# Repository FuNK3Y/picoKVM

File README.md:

# PicoKVM
An inexpensive network KVM that can switch USB and monitor inputs simultaneously

## Why
Samsung makes great monitors, but they often lack a KVM. The project started as a way to switch them along with the USB devices, over their network API. It was later generalized to most monitors, driven over HDMI DDC/CI by its own board, while still driving network-controlled monitors and devices.

## Features
- Switches the USB devices and the monitors' inputs together
- Drives most monitors over HDMI DDC/CI, and others (or any device: a lamp, ...) over the network
- No video goes through it: every computer is connected directly to every monitor, so HDCP, VRR, G-Sync, FreeSync, HDR, ... work natively
- Controlled from its button, a web page or an HTTP API, from any device on the network

## Hardware
picoKVM runs on its own board, designed in [`hardware/`](hardware/README.md): an ESP32-S3, a USB 3.0 switch (two computers, one peripheral port), two HDMI ports carrying DDC/CI only (no video) to switch monitor inputs, an RGB status LED, and a Grove port for an [M5Stack key unit](https://shop.m5stack.com/products/mechanical-key-button-unit) as the switch button.

The original build (M5Stack AtomS3 Lite + USB multiplexer) is no longer supported; its last version is [5d5997c](https://github.com/FuNK3Y/picoKVM/tree/5d5997c).

## Install
1. Open the **[browser installer](https://funk3y.github.io/picoKVM/)** in Chrome or Edge, and plug the board's AUX / FLASH USB-C port into the computer.
2. Install, then connect the board to your Wi-Fi from the same page.
3. *Visit device* opens the [settings page](#settings): set the [admin password](#admin-password) first, then the input names and the monitors.

## Wiring
- Computers' video goes directly to the monitors, as without a KVM.
- Each computer's USB goes to the board; the keyboard and mouse go to its peripheral port, through a hub (the monitor's own hub works).
- For monitors driven over DDC/CI, an HDMI cable goes from one of the board's HDMI ports to the monitor. It carries only the input-switch commands, no video. Monitors driven over the network need none.

```mermaid
graph LR
    KB["Keyboard"] <--> |USB| HUB["USB hub"]
    MOUSE["Mouse"] <--> |USB| HUB
    KVM <--> |USB| HUB
    PC1["Computer 1"] --> |Video| MON["Monitor"]
    PC2["Computer 2"] --> |Video| MON
    PC1 <--> |USB| KVM["picoKVM"]
    PC2 <--> |USB| KVM
    KVM -.-> |"HDMI (DDC/CI only)"| MON
    style MON fill:#f9f,stroke:#333
    style KVM fill:#bbf,stroke:#333
    style HUB fill:#ddd,stroke:#333
    style KB fill:#ddd,stroke:#333
    style MOUSE fill:#ddd,stroke:#333
    style PC1 fill:#ddd,stroke:#333
    style PC2 fill:#ddd,stroke:#333
```

## Settings
The settings page (*Settings*, below the switch button at `http://picokvm.local`) edits everything: Wi-Fi, input names and colors, LED brightness, admin password, monitors and [updates](#updates).

### Admin password
Once set, the admin password protects everything the settings page does: opening it, reading and changing the configuration, and installing updates, from the page or through the API. The browser asks for it (any user name); API calls send it as HTTP Basic credentials, e.g. `curl -u admin:<password>`. Switching inputs, the state and `/metrics` stay open.

**Until it is set, all of that is open to anyone on the network.**

To remove it, use *Clear password*, then *Save*, on the settings page, or send `"admin_password": null` to `/api/config`; everything above is then open again.

It travels over plain HTTP, so anyone able to watch the network traffic can read it.

### Monitors
Monitors are added on the settings page: a form for DDC/CI monitors, JSON for the others ([`config.example.json`](config.example.json) has an example of each).

#### DDC/CI monitors
Enable DDC/CI in the monitor's menu. For each computer, choose the monitor input it is on. The settings page reads the monitor: its name, the input it is on now, and the inputs it lists, named as the MCCS standard names them (VCP `0x60`: `15` DisplayPort 1, `17` HDMI 1, ...). Some monitors use other values, or name their ports differently: put the monitor on each computer's input by hand, and the page shows which value it is (*Other value...* takes any number). *Power the monitor on first* wakes up monitors that keep DDC/CI alive in standby.

The monitor must accept DDC/CI on an input that is not the active one, since it is showing the other computer when the command arrives. Most do: tested on **AOC, Samsung, Dell, Acer, Philips and Lenovo** monitors. Some have no DDC/CI at all (the Samsung G80SD): drive those over the network.

#### Samsung monitors over the network
For Samsung smart monitors without DDC/CI, the KVM sends remote-control key presses: enable IP remote on the monitor *(Connection > Network > Expert Settings)*. Find a repeatable sequence of keys that selects each input from the home screen, and write it with the [key codes](https://github.com/ollo69/ha-samsungtv-smart/blob/master/docs/Key_codes.md) as a `SamsungMonitor`. `KEY_RETURN` first also wakes the monitor up; `command_delay` (or a `delay` on one key) slows the sequence down if the menu cannot keep up.

#### Other network devices
A `GenericDevice` sends an HTTP request for each input: another monitor's API (e.g. [SmartThings](https://github.com/ollo69/ha-samsungtv-smart/issues/274#issuecomment-2597627685), untested), a lamp, ...

## Use
Switch with the button, the web page at `http://picokvm.local` (it follows the KVM whoever switches it), or the API:
```sh
curl -X POST http://picokvm.local/api/active_input/A   # or B; without the input, toggles
curl http://picokvm.local/api/active_input             # the state: active input, switching, last error
curl http://picokvm.local/api/events                   # the state as server-sent events, on every change
```
`/api/config` reads (`GET`) and writes (`POST`) the configuration, without the passwords, only `admin_password_set` tells whether one is set ([admin password](#admin-password) required). `/metrics` gives Wi-Fi signal, memory, USB power and version for Prometheus.

`picokvm` is the default hostname; it can be changed in the settings.

## Updates
*Check for updates*, then *Install*, on the settings page installs the latest [release](https://github.com/FuNK3Y/picoKVM/releases) over the network; *Upload* installs a `firmware-ota.bin` of your own. Settings are kept. The first boot of an update is a trial: if the device is not back on Wi-Fi within 2 minutes, it returns to the previous firmware.

The same through the API, with the [admin password](#admin-password):
```sh
curl -u admin:<admin_password> -X POST http://picokvm.local/api/update/latest
curl -u admin:<admin_password> --data-binary @firmware-ota.bin http://picokvm.local/api/update
```

MicroPython does not check GitHub's certificate when downloading a release: the SHA-256 GitHub publishes only guards against a corrupted download.

## ESPHome
The board can also run [ESPHome](https://esphome.io) instead of this firmware, for a native Home Assistant integration (DDC/CI monitors only). Include the [esphome/picokvm.yaml](esphome/picokvm.yaml) package, then name the computers and set the number of monitors:

```yaml
packages:
  picokvm: github://FuNK3Y/picoKVM/esphome/picokvm.yaml@main

substitutions:
  inputs:
    a: Work laptop
    b: Gaming PC
  monitors: 2
```

Each monitor's input values and the LED colors and brightness are then set from Home Assistant. [esphome/example.yaml](esphome/example.yaml) is a complete starting point; it builds, but has not been run on a board yet.

## Development
[`firmware/build.sh`](firmware/build.sh) builds MicroPython with `src/` frozen in, into `firmware/build/` (needs [ESP-IDF](https://docs.espressif.com/projects/esp-idf/en/v5.5.2/esp32s3/get-started/) v5.5.2):
```sh
. $IDF_PATH/export.sh
firmware/build.sh
```
CI runs the same build on pull requests and `main` and keeps the images as an artifact. A `v*` tag publishes a release and the [installer](install/index.html) to GitHub Pages.

The tests run the application on CPython, with stand-ins for the board ([`tests/mocks.py`](tests/mocks.py)); CI requires 95% coverage:
```sh
python3 -m unittest discover -s tests
```

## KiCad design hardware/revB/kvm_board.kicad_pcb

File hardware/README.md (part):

# picoKVM board — ESP32-S3 USB 3.0 KVM switch with HDMI DDC/CI

Two PCs (USB 3.0 Type-B) share one peripheral port (USB 3.0 Type-A).  An
ESP32-S3 flips the USB path and tells both monitors to change input over
HDMI DDC/CI.  The HDMI ports carry DDC/+5V only — video goes straight
from the PCs to the monitors.  The firmware is the MicroPython code in
`src/`, built into a MicroPython image by `firmware/` (see the main [README](../README.md)).

## Rev A release (ordered 2026-10-03, JLCPCB)

`revA/` holds the board exactly as it was sent to JLCPCB.  Freerouting is not
deterministic, so **`revA/kvm_board.kicad_pcb` is the design of record**: a
fresh `./build.sh` produces an equivalent board, not the same copper.

| file | what |
|---|---|
| `revA/kvm_board.kicad_pcb` / `.kicad_pro` / `.kicad_dru` | routed board (KiCad 10), its net classes and JLC design rules |
| `revA/jlcpcb/gerbers.zip`, `bom.csv`, `cpl.csv` | the files uploaded to JLCPCB (126 × 75 mm customer panel) |
| `revA/schematic_review.html` | readable schematic: every pin, its net and what else is on it |
| `revA/mechanical.txt` | connector, LED and button positions for the enclosure |
| `revA/thermal_justification.md` | proof that every single-spoke GND pad reaches the In1 plane |
| `revA/impedance.txt` | field-solver results for the 90 Ω pairs on JLC04161H-3313 |
| `revA/img/` | renders (top, bottom, iso, panel) and the Grove J8 pinout |

JLC order settings: 4 layers, 1.6 mm, **specified stackup JLC04161H-3313**,
no impedance control (accepted risk for prototypes, see below), 0.3 mm vias,
1 oz outer / 0.5 oz inner, flying-probe test, Standard PCBA top side,
**edge rails added by customer**, confirm production file and parts placement.

To regenerate the order files from the released board without re-routing:

```
mkdir -p out && cp revA/kvm_board.kicad_* out/
./build.sh fab        # panel (hw/panel.py), Gerbers, PTH/NPTH drill, BOM, CPL -> out/jlcpcb/
```

## Rev B (order files ready, branch `rev-b`)

`revB/` holds the board as it is to be sent to JLCPCB.  As for rev A,
**`revB/kvm_board.kicad_pcb` is the design of record**: `./build.sh` routed
it to 6 open connections, and the last ones were closed by hand on the routed
board (local rip-up and re-lay of a few control lines around the hub's
north-east pins and the RP2350's QSPI bus, gap joins on the VBUS trunks, port
3's VBUS widened in place, three dangling vias removed).  A fresh build gives
an equivalent placement, not this copper.

| file | what |
|---|---|
| `revB/kvm_board.kicad_pcb` / `.kicad_pro` / `.kicad_dru` | routed board (KiCad 10): DRC 0 errors, 0 unconnected, `checks.py` passed |
| `revB/jlcpcb/gerbers.zip`, `bom.csv`, `cpl.csv` | order files (112 × 102 mm customer panel, rails left and right), JLC DFM checked 2026-11-16 |
| `revB/schematic_review.html` | readable schematic |
| `revB/mechanical.txt` | connector, LED and button positions for the enclosure |
| `revB/impedance.txt` | field-solver results for the 90 Ω pairs |
| `revB/img/` | renders (top, bottom, iso) |

JLC DFM on these files (2026-11-16): the red items are understood and
accepted: pad-to-track 0.073–0.10 mm at 0402 pad corners (JLC reads KiCad's
rounded pads as sharp rectangles; KiCad DRC checks the real shape at 0.1 mm),
0.075 mm via annular rings (JLC minimum 0.05 mm), THT-to-SMD spacing at the
HDMI stacks, thermal vias under the RP2350, edge connectors at the edge, and
lead-edge flags on fine-pitch parts ("pin without pad" and "missing hole" are
0).  Check the J1/U11 and J8/J11 3D-model collision warnings in JLC's viewer
before ordering.  Order settings as rev A (4 layers, JLC04161H-3313, top-side
Standard PCBA, edge rails added by customer).

Port supply path (DC resistance of the routed copper, 1 oz outer, from
`revB/kvm_board.kicad_pcb`): USB A J1 → U4 34 mΩ, U32 → port switches
40–64 mΩ, switches → connectors 8–66 mΩ (port 3 66 mΩ); with all four ports
at 1 A, VBUS_HUB drops 111–152 mV.  Rev B's first routing measured ~0.5 Ω
PC-to-port before the 1 mm trunks (`hw/route_nets.py` POWER_TRUNKS).

Hub decoupling: the TUSB8041's +1V1 pins drop through vias onto a B.Cu ring
under the package; C71 sits in the hub's south-west corner (U43 moved down
its USB 2.0 line to make room), 3–8 mm from the west-side pins 5/8/13/21.  A
north-west corner capacitor was tried and dropped: it left the hub's
east-side control lines unroutable.

Rev B adds a TUSB8041 hub with four downstream ports (two stacked USB 3.0
Type-A, J3 and J10), an RP2350 that can intercept the keyboard on port 4,
**four HDMI DDC/CI ports on two stacked connectors** (J5, J6: Foxconn
QJ11191-DFB2-4H) and a TCA9548A I2C multiplexer for the four DDC buses, the
hub's SMBus and a second Grove port.
Pinout changes are under "Rev B: differences from rev A" below.  Several rev A
sections further down no longer describe this board:

| rev A statement below | rev B |
|---|---|
| Board 112 × 75 mm | **98 × 102 mm**, same 4-layer JLC04161H-3313 stackup, top-side assembly |
| Two single HDMI receptacles | Two stacked HDMI receptacles: J5 lower = HDMI 1, upper = HDMI 3; J6 lower = HDMI 2, upper = HDMI 4 (each port with its own 100 mA PTC, USBLC6 and 2k pull-ups; one LM66100 per connector feeds both its ports) |
| No AC-coupling caps on the SuperSpeed lines | The hub's downstream and upstream TX pairs are AC-coupled on the board (C60–C69); the PC-side mux path is unchanged |
| All SuperSpeed pairs on F.Cu | Ports 1/3 RX pairs run partly on B.Cu (referenced to In2 +3V3) |
| ESP32 footprint is the only exposed pad with vias | U30 (hub) and U45 (RP2350) use KiCad's ThermalVias footprints |
| U5 AP2112K LDO, one peripheral port behind U20 | 3.3 V and 1.1 V from two TLV62569 bucks (U5, U31); one TPS2553 per port (U33–U36) behind U32 |
| Prototype test plan (rev A) | see the rev B envelope below |

How the rev B board is laid out and routed, in addition to "How the board is
routed": capacitors and resistors that belong at a pin are tagged in the
schematic (`at=(ref, pin)` in `hw/kvm_board.py`) and placed there by
`make_pcb.py`; `layout.py` keeps routing corridors free of passives (pairs,
the hub's east-side lines, the RP2350's USB escape); `hw/route_nets.py`
pre-routes the nets Freerouting kept leaving open (regulator switch nodes and
feedback, both crystals, the hub's port-control lines, QSPI, the RP2350's USB)
and ties the +1V1 vias into one tree.  The CPL check in `make_fab.py` compares
JLC's pin names with ours (`hw/lib/jlcref/lcsc_pins.json`) and turns D5
(C2286, whose JLC symbol numbers the anode as pin 1) by 180°.

### Rev B prototype power envelope

The four ports can ask for more current than the board's shared supply path
can give: four TPS2553 limits (1.2–1.38 A each) behind one TPS2116 (2.5 A
class), fed by one PC port (0.9 A for USB 3) or the AUX input, and U32 falls
back from AUX to the selected PC the moment AUX goes away.  There is no
aggregate current limit.  Until that is designed in, rev B prototypes are run
inside this envelope:

- **Downstream load, all four ports together: ≤ 0.5 A** (keyboard, mouse and
  low-current devices), whether or not AUX is plugged in, since unplugging
  AUX moves the whole load onto the selected PC.  Measure the board's own
  current on the first prototype and lower the 0.5 A by whatever it exceeds
  0.35 A.
- **No bus-powered drives, chargers or four-port full-load tests, not even
  from a strong bench supply on AUX:** the load still goes through U32 (2.5 A
  class) and the board's shared copper, and falls back onto the selected PC
  when AUX is unplugged.  A higher-current experiment needs its own test plan
  (current-limited source, no PC attached).  Start with no downstream load
  until the board's own current has been measured in its operating states
  (idle, all HDMI monitors attached, Grove modules, ESP32 Wi-Fi active).
- **Grove I2C (J11):** only modules powered from the board's own J11 5 V.  An
  independently powered module with pull-ups to its own 5 V leaks ~0.2 mA per
  line into +3V3, or ~0.5 mA into an unpowered board.
- **HDMI +5 V (pin 18):** measure it with each monitor; it can fall below the
  4.8 V minimum from a weak PC port, as on rev A.  Four monitors can draw up
  to 4 × 55 mA = 0.22 A from +5V_SYS: count it in the board's own current.
- **Port power-off is not a power cycle:** the TPS2553s have no output
  discharge, so a port's 44 µF can hold VBUS well past 200 ms with a light
  load.  Firmware treats a hub reset / port disable as a data disconnect only.
- **Bring-up checks beyond rev A's:** hub enumeration from cold several times
  (crystal start-up); USB 3 and USB 2 throughput on every port; VBUS at each
  port at 0.5 A; scope +5V_SYS and VBUS_HUB when plugging the PCs and AUX one
  after another (inrush: ~30 µF on +5V_SYS and 210 µF on VBUS_HUB with no
  current limit), on a protected source.

## Build

```
./build.sh          # netlist + ERC, PCB, routing, DRC, renders, JLCPCB files (all in Docker)
./build.sh noroute  # same, stopping at the placed, unrouted board
./build.sh reroute  # route the board in out/ as placed (placement runs may reorder footprints, which changes routing)
./build.sh autoroute  # one more Freerouting pass on the board in out/
./build.sh parts    # re-import the LCSC symbols/footprints/3D models
./build.sh shell    # shell inside the toolchain (KiCad 10 + SKiDL + easyeda2kicad)
```

Sources:

| file | what |
|---|---|
| `hw/kvm_board.py` | the schematic, as SKiDL code — edit this, not the netlist |
| `hw/make_pcb.py` | builds the 4-layer `.kicad_pcb`: placement, planes, net classes, JLC rules |
| `hw/route_ss.py` | hand-designed USB 3.0 SuperSpeed pairs (coupled, matched, no vias) |
| `hw/route_usb2.py` | hand-designed USB 2.0 pairs (coupled, matched, symmetric via pairs) |
| `hw/finish.py` | power neck-downs + plane fanout before routing; GND stitching after |
| `hw/layout.py` | rev B placement: anchors, hand-placed passives, passive-free corridors, board size |
| `hw/placement_freeze.py` | frozen passive spots from an earlier placement, so routing-relevant positions stay put |
| `hw/pairs.py`, `hw/route_pairs.py` | rev B pair router and the hub's SuperSpeed / USB 2.0 pairs |
| `hw/route_nets.py` | grid pre-router for nets Freerouting left open, the 1 mm VBUS trunks and the +1V1 tree |
| `hw/plot.py` | 2-D plan of a board window (`out/img/plan.svg`) for layout work |
| `hw/route.py` | Freerouting round-trip (Specctra DSN/SES) for everything else |
| `hw/impedance.py` | 2-D field solver for the 90 Ω pairs on the JLC 3313 stackup |
| `hw/make_fab.py` | JLCPCB `bom.csv` / `cpl.csv` (CPL expressed in JLC's own footprint frame) |
| `hw/panel.py` | JLC assembly panel: rails, mouse bites, fiducials, tooling holes |
| `hw/thermal_report.py` | proves every single-spoke GND pad reaches the In1 plane |
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
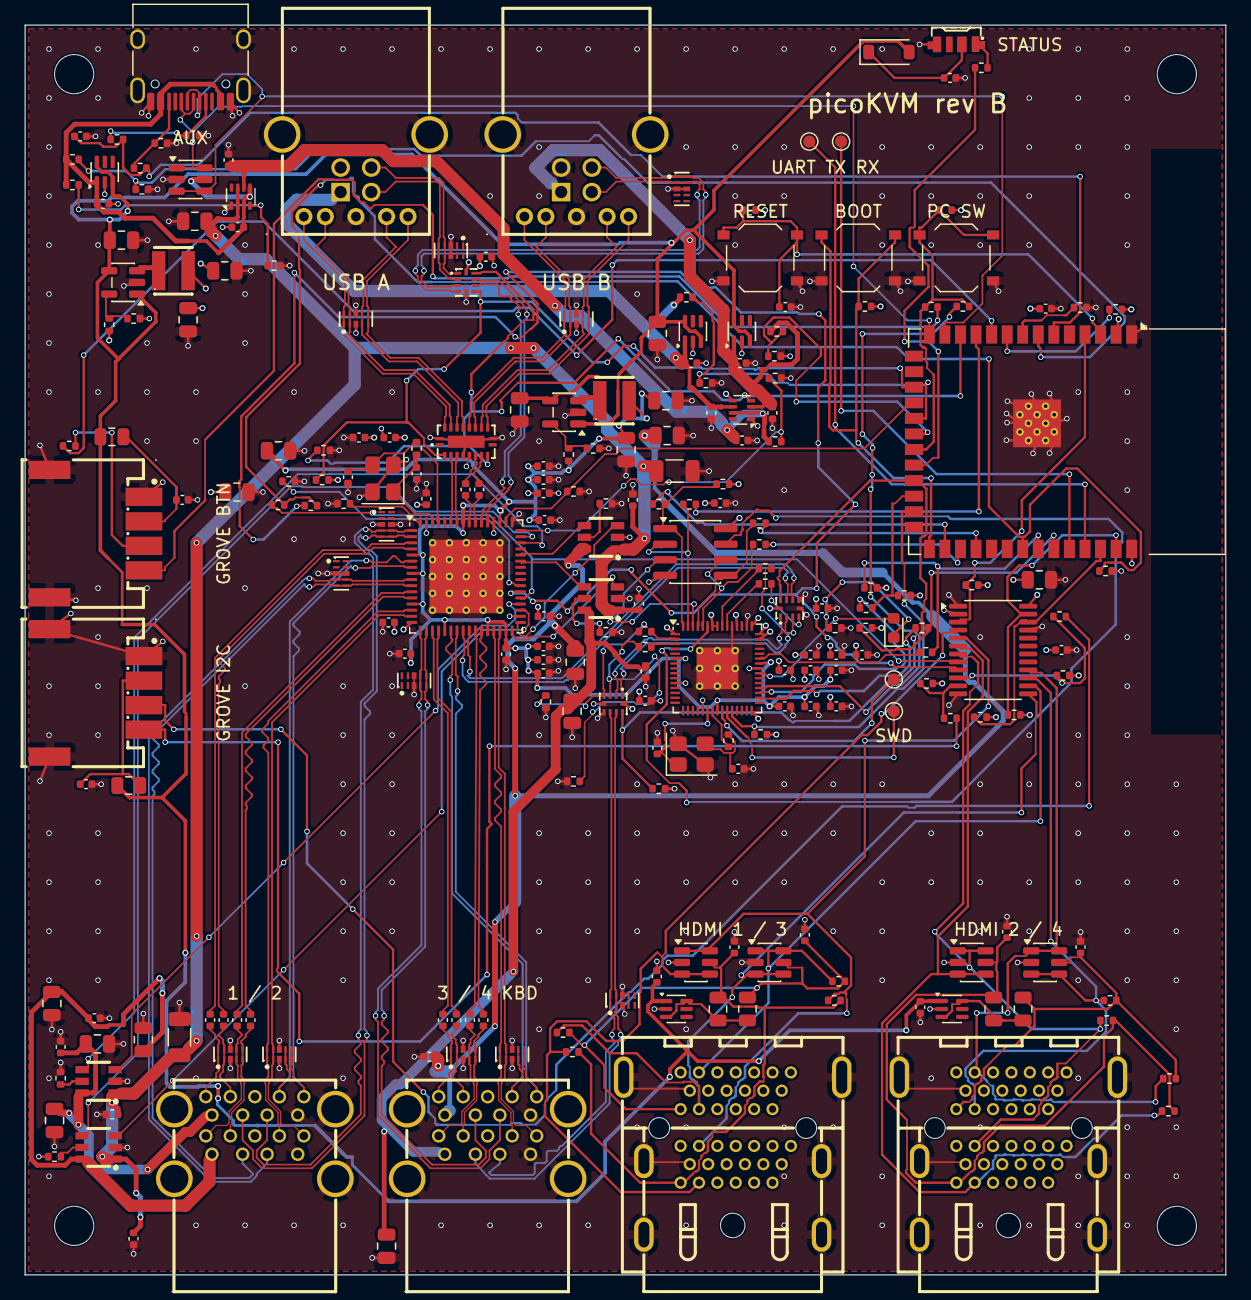
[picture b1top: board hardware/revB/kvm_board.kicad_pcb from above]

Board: 4 copper layers, 98.0 x 102.0 mm, 239 parts (0 on the bottom side), 175 nets.

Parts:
C3, C60, C61, C62, C63, C64, C65, C66, C67, C68, C69, C70, C71, C72, C73, C74, C75, C76, C77, C78, C79, C80, C81, C84, C85, C86, C87, C88, C89, C90, C92, C100, C101, C138, C141, C142, C145, C146, C149, C150, C153, C165, C167, C169, C171, C183, C184, C185, C187, C189, C190, C191, C192: 100nF; C_0402_1005Metric
C4, C5, C6, C7, C23, C24, C26, C27, C102, C164, C166, C188: 1uF; C_0402_1005Metric
C8, C25, C82, C83, C158, C159, C160, C161, C162, C163: 10uF; C_0805_2012Metric
C9, C10: 100uF; C_1206_3216Metric
C91: 4.7uF; C_0402_1005Metric
C114, C115: 18pF; C_0402_1005Metric
C139, C140, C143, C144, C147, C148, C151, C152, C186: 22uF; C_0805_2012Metric
C181, C182: 15pF; C_0402_1005Metric
D3: SK6812SIDE-A; LED-SMD_4P-L4.0-W1.6-L
D4: 1N4148W; D_SOD-123
D5: KBD; LED_0603_1608Metric
F2, F3, F4, F5, F6, F7: 100mA; Fuse_0805_2012Metric
H1, H2, H3, H4: MountingHole; MountingHole_3.2mm_M3
J1, J2: HC-USB3.0-L1845-BF; USB-B-TH_9P-L18.5-W12.0
J3, J10: HC-USB3.0-L175-2X1-P; USB-A-TH_H181-AF2R06-12ALCR
J4: USB_C_Receptacle_USB2.0_16P; USB_C_Receptacle_HRO_TYPE-C-31-M-12
J5, J6: QJ11191-DFB2-4H; HDMI-TH_QJ11191-DFB1-4F
J8: GROVE_BTN; CONN-SMD_4P-P2.00_ZX-HY2.0-4PWT
J11: GROVE_I2C; CONN-SMD_4P-P2.00_ZX-HY2.0-4PWT
L1, L2: 2.2uH; IND-SMD_L3.0-W3.0
R1, R2: 5.1k; R_0402_1005Metric
R3, R4, R22: 100k; R_0402_1005Metric
R5, R6, R11, R14, R17, R24, R26, R28, R30, R41, R46, R49, R51, R53, R55, R62, R63, R64, R65, R66, R72: 10k; R_0402_1005Metric
R7: 9.53k; R_0402_1005Metric
R8, R15, R40, R42, R43, R44, R45, R54: 1k; R_0402_1005Metric
R9: 1M; R_0402_1005Metric
R10: 90.9k; R_0402_1005Metric
R12, R13, R70, R71, R73, R74: 4.7k; R_0402_1005Metric
R16: 33k; R_0402_1005Metric
R18, R19, R20, R21: 20k; R_0402_1005Metric
R23: 22k; R_0402_1005Metric
R25: 12k; R_0402_1005Metric
R27, R29, R31: 15k; R_0402_1005Metric
R32, R33, R34, R35, R36, R37, R38, R39: 2k; R_0402_1005Metric
R47, R48, R50, R52: 220; R_0402_1005Metric
R56, R57, R60, R61: 27; R_0402_1005Metric
R58, R59: 8.2k; R_0402_1005Metric
R67, R68, R69, R75, R76: 100; R_0402_1005Metric
SW1: RESET; SW_Push_1P1T_XKB_TS-1187A
SW2: BOOT; SW_Push_1P1T_XKB_TS-1187A
SW3: SWITCH; SW_Push_1P1T_XKB_TS-1187A
TP1: SWCLK; TestPoint_Pad_D1.0mm
TP2: SWDIO; TestPoint_Pad_D1.0mm
TP3: TXD0; TestPoint_Pad_D1.0mm
TP4: RXD0; TestPoint_Pad_D1.0mm
U1: ESP32-S3-WROOM-1-N8R2; ESP32-S3-WROOM-1
U2: HD3SS3212IRKSR; DHVQFN-20_L4.5-W2.5-P0.50-BL-EP
U3, U47, U48: TS3USB221ARSER; UQFN-10_L2.0-W1.5-P0.50-BL
U4, U32: TPS2116DRL; SOT-583-8
U5, U31: TLV62569DBV; SOT-23-5
U6, U7, U8, U21, U22: LM66100DCK; SOT-363_SC-70-6
U11, U12, U17, U18, U37, U38, U39, U40, U41, U42, U43, U44: TPD4E05U06DQAR_C138714; USON-10_L2.5-W1.0-P0.50-BL
U13: TCA9548APWR; TSSOP-24_4.4x7.8mm_P0.65mm
U14, U15, U16, U19, U20: USBLC6-2SC6; SOT-23-6
U30: TUSB8041IRGCR; QFN-64-1EP_9x9mm_P0.5mm_EP6x6mm_ThermalVias
U33, U34, U35, U36: TPS2553DBVR; SOT-23-6_L2.9-W1.6-P0.95-LS2.8-BR
U45: RP2350A; QFN-60-1EP_7x7mm_P0.4mm_EP3.4x3.4mm_ThermalVias
U46: W25Q32JVSNIQ; SOIC-8_3.9x4.9mm_P1.27mm
Y1: 24MHz; Crystal_SMD_3225-4Pin_3.2x2.5mm
Y2: ABM8-272-T3; Crystal_SMD_3225-4Pin_3.2x2.5mm

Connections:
+1V1: C70.1, C71.1, C72.1, C73.1, C74.1, C75.1, C76.1, C77.1, C82.1, C88.1, C89.1, C90.1, C162.1, C163.1, L2.2, R24.1, U30.5, U30.8, U30.13, U30.21, U30.28, U30.31, U30.51, U30.57, U45.6, U45.23, U45.39
+3V3: C3.1, C78.1, C79.1, C80.1, C81.1, C83.1, C84.1, C85.1, C86.1, C87.1, C91.1, C92.1, C101.1, C102.1, C159.1, C160.1, C183.1, C184.1, C185.1, C186.1, C187.1, C191.1, L1.2, R6.2, R22.1, R41.2, R46.2, R49.2, R51.2, R53.2, R62.2, R63.2, R64.2, R66.2, R70.2, R71.2, R72.2, R73.2, R74.2, U1.2, U2.6, U3.10, U4.5, U13.24, U30.16, U30.34, U30.52, U30.63, U45.1, U45.11, U45.20, U45.30, U45.38, U45.44, U45.45, U45.46, U45.49, U45.53, U45.54, U46.8, U47.10, U48.10
+5V_SYS: C25.1, C158.1, C161.1, C164.1, C166.1, D4.2, F4.1, F5.1, U5.1, U5.4, U6.3, U6.6, U7.3, U7.6, U8.3, U8.6, U21.1, U22.1, U31.1, U31.4
AUX_CC1: J4.A5, R1.1, R3.1
AUX_CC2: J4.B5, R2.1, R4.1
AUX_CC_SENSE: C100.1, R3.2, R4.2, U1.6
AUX_DN: J4.A7, J4.B7, U1.13, U14.3, U14.4
AUX_DP: J4.A6, J4.B6, U1.14, U14.1, U14.6
AUX_PR1: R16.2, R17.1, U32.4
BOARD_REV: R65.1, U1.8
BOOT: R63.1, SW2.1, U1.27
BTN_SWITCH: R47.2, R64.1, R68.1, SW3.1, U1.21
EN: C188.1, R62.1, SW1.1, U1.3
EXT_LED: R69.1, U1.10
GND: C3.2, C4.2, C5.2, C6.2, C7.2, C8.2, C9.2, C10.2, C23.2, C24.2, C25.2, C26.2, C27.2, C70.2, C71.2, C72.2, C73.2, C74.2, C75.2, C76.2, C77.2, C78.2, C79.2, C80.2, C81.2, C82.2, C83.2, C84.2, C85.2, C86.2, C87.2, C88.2, C89.2, C90.2, C91.2, C92.2, C100.2, C101.2, C102.2, C114.2, C115.2, C138.2, C139.2, C140.2, C141.2, C142.2, C143.2, C144.2, C145.2, C146.2, C147.2, C148.2, C149.2, C150.2, C151.2, C152.2, C153.2, C158.2, C159.2, C160.2, C161.2, C162.2, C163.2, C164.2, C165.2, C166.2, C167.2, C169.2, C171.2, C181.2, C182.2, C183.2, C184.2, C185.2, C186.2, C187.2, C188.2, C189.2, C190.2, C191.2, C192.2, D3.4, J1.4, J1.7, J1.10, J1.11, J2.4, J2.7, J2.10, J2.11, J3.4, J3.7, J3.13, J3.16, J3.19, J3.20, J4.A1, J4.A12, J4.B1, J4.B12, J4.SH, J5.0, J5.17, J5.P17, J6.0, J6.17, J6.P17, J8.1, J8.5, J8.6, J10.4, J10.7, J10.13, J10.16, J10.19, J10.20, J11.1, J11.5, J11.6, R1.2, R2.2, R5.2, R7.2, R8.2, R11.2, R14.2, R15.2, R17.2, R18.2, R19.2, R20.2, R21.2, R23.2, R25.2, R27.2, R29.2, R31.2, R54.2, R55.2, R58.2, R59.2, R65.2, SW1.2, SW2.2, SW3.2, U1.1, U1.40, U1.41, U2.5, U2.11, U2.20, U2.21, U3.5, U4.1, U5.2, U6.2, U7.2, U8.2, U11.3, U11.8, U12.3, U12.8, U13.1, U13.2, U13.12, U13.21, U14.2, U15.2, U16.2, U17.3, U17.8, U18.3, U18.8, U19.2, U20.2, U21.2, U22.2, U30.49, U30.65, U31.2, U32.1, U33.2, U34.2, U35.2, U36.2, U37.3, U37.8, U38.3, U38.8, U39.3, U39.8, U40.3, U40.8, U41.3, U41.8, U42.3, U42.8, U43.3, U43.8, U44.3, U44.8, U45.47, U45.50, U45.61, U46.4, U47.5, U47.6, U48.5, U48.6, Y1.2, Y1.4, Y2.2, Y2.4
GROVE2_5V: C192.1, F5.2, J11.2
GROVE_5V: C190.1, F4.2, J8.2
GROVE_BTN: J8.4, R68.2
GROVE_LED: J8.3, R69.2
GROVE_SCL: R74.1, R76.1, U13.11
GROVE_SCL_C: J11.4, R76.2
GROVE_SDA: R73.1, R75.1, U13.10
GROVE_SDA_C: J11.3, R75.2
H1_SSTX_N: C63.1, U30.4
H1_SSTX_P: C62.1, U30.3
H2_SSTX_N: C65.1, U30.12
H2_SSTX_P: C64.1, U30.11
H3_SSTX_N: C67.1, U30.20
H3_SSTX_P: C66.1, U30.19
H4_DN: U30.25, U48.7
H4_DP: U30.24, U48.8
H4_SSTX_N: C69.1, U30.27
H4_SSTX_P: C68.1, U30.26
HDMI1_5V: C165.1, F2.2, J5.18, R32.2, R33.2, U15.5
HDMI1_5V_D: F2.1, F6.1, U21.3, U21.6
HDMI1_SCL: J5.15, R32.1, U13.5, U15.1, U15.6
HDMI1_SDA: J5.16, R33.1, U13.4, U15.3, U15.4
HDMI2_5V: C167.1, F3.2, J6.18, R34.2, R35.2, U16.5
HDMI2_5V_D: F3.1, F7.1, U22.3, U22.6
HDMI2_SCL: J6.15, R34.1, U13.7, U16.1, U16.6
HDMI2_SDA: J6.16, R35.1, U13.6, U16.3, U16.4
HDMI3_5V: C169.1, F6.2, J5.P18, R36.2, R37.2, U19.5
HDMI3_SCL: J5.P15, R36.1, U13.14, U19.1, U19.6
HDMI3_SDA: J5.P16, R37.1, U13.13, U19.3, U19.4
HDMI4_5V: C171.1, F7.2, J6.P18, R38.2, R39.2, U20.5
HDMI4_SCL: J6.P15, R38.1, U13.16, U20.1, U20.6
HDMI4_SDA: J6.P16, R39.1, U13.15, U20.3, U20.4
HUB_CFG: R12.2, R13.2, R14.1, U1.33
HUB_R1: R7.1, U30.64
HUB_RESET_N: R8.1, U1.18, U30.50
HUB_SCL: R12.1, U13.9, U30.38
HUB_SDA: R13.1, U13.8, U30.37
HUB_SMBUSZ: R15.1, U30.39
HUB_VBUS_DET: R10.2, R11.1, U30.48
HUB_XI: C114.1, R9.1, U30.62, Y1.1
HUB_XO: C115.1, R9.2, U30.61, Y1.3
I2C_MUX_RESET_N: R72.1, U1.4, U13.3
I2C_SCL: R71.1, U1.38, U13.22
I2C_SDA: R70.1, U1.39, U13.23
KBD_DN: R61.2, U48.4
KBD_DP: R60.2, U48.3
KBD_INTERCEPT: R55.1, U1.23, U47.9, U48.9
KBH_DN: R57.2, R59.1, U47.3
KBH_DP: R56.2, R58.1, U47.4
KBT_DN: U47.1, U48.2
KBT_DP: U47.2, U48.1
LED_DIN: D3.1, R67.2
LED_RGB: R67.1, U1.22
LED_VDD: C189.1, D3.2, D4.1
P1_DN: J3.11, U30.2, U41.5, U41.6
P1_DP: J3.12, U30.1, U41.4, U41.7
P1_ILIM: R18.1, U33.5
P1_OC_N: U30.46, U33.4
P1_PWR_EN: U30.36, U33.3
P1_SSRX_N: J3.14, U30.7, U38.5, U38.6
P1_SSRX_P: J3.15, U30.6, U38.4, U38.7
P1_SSTX_N: C63.2, J3.17, U37.2, U37.9
P1_SSTX_P: C62.2, J3.18, U37.1, U37.10
P2_DN: J3.2, U30.10, U42.5, U42.6
P2_DP: J3.3, U30.9, U42.4, U42.7
P2_ILIM: R19.1, U34.5
P2_OC_N: U30.47, U34.4
P2_PWR_EN: U30.35, U34.3
P2_SSRX_N: J3.5, U30.15, U38.2, U38.9
P2_SSRX_P: J3.6, U30.14, U38.1, U38.10
P2_SSTX_N: C65.2, J3.8, U37.5, U37.6
P2_SSTX_P: C64.2, J3.9, U37.4, U37.7
P3_DN: J10.11, U30.18, U43.5, U43.6
P3_DP: J10.12, U30.17, U43.4, U43.7
P3_ILIM: R20.1, U35.5
P3_OC_N: U30.44, U35.4
P3_PWR_EN: U30.33, U35.3
P3_SSRX_N: J10.14, U30.23, U40.5, U40.6
P3_SSRX_P: J10.15, U30.22, U40.4, U40.7
P3_SSTX_N: C67.2, J10.17, U39.2, U39.9
P3_SSTX_P: C66.2, J10.18, U39.1, U39.10
P4_DN: J10.2, U44.2, U44.9, U47.8
P4_DP: J10.3, U44.1, U44.10, U47.7
P4_ILIM: R21.1, U36.5
P4_OC_N: U30.43, U36.4
P4_PWR_EN: U30.32, U36.3
P4_SSRX_N: J10.5, U30.30, U40.2, U40.9
P4_SSRX_P: J10.6, U30.29, U40.1, U40.10
P4_SSTX_N: C69.2, J10.8, U39.5, U39.6
P4_SSTX_P: C68.2, J10.9, U39.4, U39.7
PCA_DN: J1.2, U3.2, U11.5, U11.6
PCA_DP: J1.3, U3.1, U11.4, U11.7
PCA_SSRX_N: J1.8, U2.18, U17.2, U17.9
PCA_SSRX_P: J1.9, U2.19, U17.1, U17.10
PCA_SSTX_N: J1.5, U2.16, U17.5, U17.6
PCA_SSTX_P: J1.6, U2.17, U17.4, U17.7
PCB_DN: J2.2, U3.4, U12.2, U12.9
PCB_DP: J2.3, U3.3, U12.1, U12.10
PCB_SSRX_N: J2.8, U2.14, U18.2, U18.9
PCB_SSRX_P: J2.9, U2.15, U18.1, U18.10
PCB_SSTX_N: J2.5, U2.12, U18.5, U18.6
PCB_SSTX_P: J2.6, U2.13, U18.4, U18.7
PERIPH_FAULT_N: R66.1, U1.9
RP_GPIO20: R48.1, U45.32
RP_GPIO21: R50.1, U45.33
RP_GPIO22: R47.1, U45.34
RP_GPIO26: R52.1, U45.40
RP_HOST_DN: R57.1, U45.3
RP_HOST_DP: R56.1, U45.2
RP_LED: D5.2, U45.37
RP_LED_K: D5.1, R54.1
RP_LINK_ATTN: R52.2, R53.1, U1.34
RP_LINK_RX: R50.2, R51.1, U1.24
RP_LINK_TX: R48.2, R49.1, U1.35
RP_PROG_SCLK: R43.2, U1.29
RP_PROG_SD0: R44.2, U1.30
RP_PROG_SD1: R45.2, U1.11
RP_PROG_SS: R42.2, U1.28
RP_QSPI_SCLK: R43.1, U45.56, U46.6
RP_QSPI_SD0: R44.1, U45.57, U46.5
RP_QSPI_SD1: R45.1, U45.59, U46.2
RP_QSPI_SD2: U45.58, U46.3
RP_QSPI_SD3: U45.55, U46.7
RP_QSPI_SS: R41.1, R42.1, U45.60, U46.1
RP_RUN: R46.1, U1.25, U45.26
RP_SWCLK: TP1.1, U45.24
RP_SWDIO: TP2.1, U45.25
RP_USB_DN: R61.1, U45.51
RP_USB_DP: R60.1, U45.52
RP_XIN: C181.1, U45.21, Y2.1
RP_XOUT: R40.1, U45.22
RP_XOUT_R: C182.1, R40.2, Y2.3
RXD0: TP4.1, U1.36
TXD0: TP3.1, U1.37
U5_FB: R22.2, R23.1, U5.5
U5_SW: L1.1, U5.3
U31_FB: R24.2, R25.1, U31.5
U31_SW: L2.1, U31.3
UPH_SSTX_N: C61.1, U30.55
UPH_SSTX_P: C60.1, U30.56
UP_DN: U3.7, U30.54
UP_DP: U3.8, U30.53
UP_SSRX_N: U2.4, U30.58
UP_SSRX_P: U2.3, U30.59
UP_SSTX_N: C61.2, U2.8
UP_SSTX_P: C60.2, U2.7
USB_OE_N: R6.1, U1.17, U2.2, U3.6
USB_SEL: R5.1, U1.12, U2.9, U3.9, U4.4
VBUS_A: C4.1, C23.1, J1.1, R26.1, U4.6, U6.1
VBUS_AUX: C7.1, C26.1, J4.A4, J4.A9, J4.B4, J4.B9, R16.1, R30.1, U8.1, U14.5, U32.3, U32.5
VBUS_AUX_SENSE: R30.2, R31.1, U1.7
VBUS_A_SENSE: R26.2, R27.1, U1.19
VBUS_B: C5.1, C24.1, J2.1, R28.1, U4.3, U7.1
VBUS_B_SENSE: R28.2, R29.1, U1.20
VBUS_HUB: C8.1, C9.1, C10.1, C138.1, C142.1, C146.1, C150.1, U32.2, U32.7, U33.1, U34.1, U35.1, U36.1
VBUS_P1: C139.1, C140.1, C141.1, J3.10, U33.6
VBUS_P2: C143.1, C144.1, C145.1, J3.1, U34.6
VBUS_P3: C147.1, C148.1, C149.1, J10.10, U35.6
VBUS_P4: C151.1, C152.1, C153.1, J10.1, U36.6
VBUS_PC: C6.1, C27.1, R10.1, U4.2, U4.7, U32.6

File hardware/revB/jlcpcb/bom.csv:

Comment,Designator,Footprint,LCSC Part #
100nF,"C3,C60,C61,C62,C63,C64,C65,C66,C67,C68,C69,C70,C71,C72,C73,C74,C75,C76,C77,C78,C79,C80,C81,C84,C85,C86,C87,C88,C89,C90,C92,C100,C101,C138,C141,C142,C145,C146,C149,C150,C153,C165,C167,C169,C171,C183,C184,C185,C187,C189,C190,C191,C192",C_0402_1005Metric,C1525
1uF,"C4,C5,C6,C7,C23,C24,C26,C27,C102,C164,C166,C188",C_0402_1005Metric,C52923
10uF,"C8,C25,C82,C83,C158,C159,C160,C161,C162,C163",C_0805_2012Metric,C15850
100uF,"C9,C10",C_1206_3216Metric,C15008
4.7uF,C91,C_0402_1005Metric,C23733
18pF,"C114,C115",C_0402_1005Metric,C1549
22uF,"C139,C140,C143,C144,C147,C148,C151,C152,C186",C_0805_2012Metric,C45783
15pF,"C181,C182",C_0402_1005Metric,C1548
SK6812SIDE-A,D3,LED-SMD_4P-L4.0-W1.6-L,C5378721
1N4148W,D4,D_SOD-123,C81598
KBD,D5,LED_0603_1608Metric,C2286
100mA,"F2,F3,F4,F5,F6,F7",Fuse_0805_2012Metric,C20975
HC-USB3.0-L1845-BF,"J1,J2",USB-B-TH_9P-L18.5-W12.0,C7501849
HC-USB3.0-L175-2X1-P,"J3,J10",USB-A-TH_H181-AF2R06-12ALCR,C7501881
USB_C_Receptacle_USB2.0_16P,J4,USB_C_Receptacle_HRO_TYPE-C-31-M-12,C165948
QJ11191-DFB2-4H,"J5,J6",HDMI-TH_QJ11191-DFB1-4F,C225760
GROVE_BTN/GROVE_I2C,"J8,J11",CONN-SMD_4P-P2.00_ZX-HY2.0-4PWT,C7429571
2.2uH,"L1,L2",IND-SMD_L3.0-W3.0,C43389
5.1k,"R1,R2",R_0402_1005Metric,C25905
100k,"R3,R4,R22",R_0402_1005Metric,C25741
10k,"R5,R6,R11,R14,R17,R24,R26,R28,R30,R41,R46,R49,R51,R53,R55,R62,R63,R64,R65,R66,R72",R_0402_1005Metric,C25744
9.53k,R7,R_0402_1005Metric,C96273
1k,"R8,R15,R40,R42,R43,R44,R45,R54",R_0402_1005Metric,C11702
1M,R9,R_0402_1005Metric,C26083
90.9k,R10,R_0402_1005Metric,C26989
4.7k,"R12,R13,R70,R71,R73,R74",R_0402_1005Metric,C25900
33k,R16,R_0402_1005Metric,C25779
20k,"R18,R19,R20,R21",R_0402_1005Metric,C25765
22k,R23,R_0402_1005Metric,C25768
12k,R25,R_0402_1005Metric,C25752
15k,"R27,R29,R31",R_0402_1005Metric,C25756
2k,"R32,R33,R34,R35,R36,R37,R38,R39",R_0402_1005Metric,C4109
220,"R47,R48,R50,R52",R_0402_1005Metric,C25091
27,"R56,R57,R60,R61",R_0402_1005Metric,C25100
8.2k,"R58,R59",R_0402_1005Metric,C25924
100,"R67,R68,R69,R75,R76",R_0402_1005Metric,C25076
BOOT/RESET/SWITCH,"SW1,SW2,SW3",SW_Push_1P1T_XKB_TS-1187A,C571338
ESP32-S3-WROOM-1-N8R2,U1,ESP32-S3-WROOM-1,C2913204
HD3SS3212IRKSR,U2,DHVQFN-20_L4.5-W2.5-P0.50-BL-EP,C544517
TS3USB221ARSER,"U3,U47,U48",UQFN-10_L2.0-W1.5-P0.50-BL,C128396
TPS2116DRL,"U4,U32",SOT-583-8,C3235557
TLV62569DBV,"U5,U31",SOT-23-5,C141836
LM66100DCK,"U6,U7,U8,U21,U22",SOT-363_SC-70-6,C2869734
TPD4E05U06DQAR_C138714,"U11,U12,U17,U18,U37,U38,U39,U40,U41,U42,U43,U44",USON-10_L2.5-W1.0-P0.50-BL,C138714
TCA9548APWR,U13,TSSOP-24_4.4x7.8mm_P0.65mm,C130026
USBLC6-2SC6,"U14,U15,U16,U19,U20",SOT-23-6,C7519
TUSB8041IRGCR,U30,QFN-64-1EP_9x9mm_P0.5mm_EP6x6mm_ThermalVias,C544686
TPS2553DBVR,"U33,U34,U35,U36",SOT-23-6_L2.9-W1.6-P0.95-LS2.8-BR,C55266
RP2350A,U45,QFN-60-1EP_7x7mm_P0.4mm_EP3.4x3.4mm_ThermalVias,C42411118
W25Q32JVSNIQ,U46,SOIC-8_3.9x4.9mm_P1.27mm,C5355146
24MHz,Y1,Crystal_SMD_3225-4Pin_3.2x2.5mm,C70590
ABM8-272-T3,Y2,Crystal_SMD_3225-4Pin_3.2x2.5mm,C20625731

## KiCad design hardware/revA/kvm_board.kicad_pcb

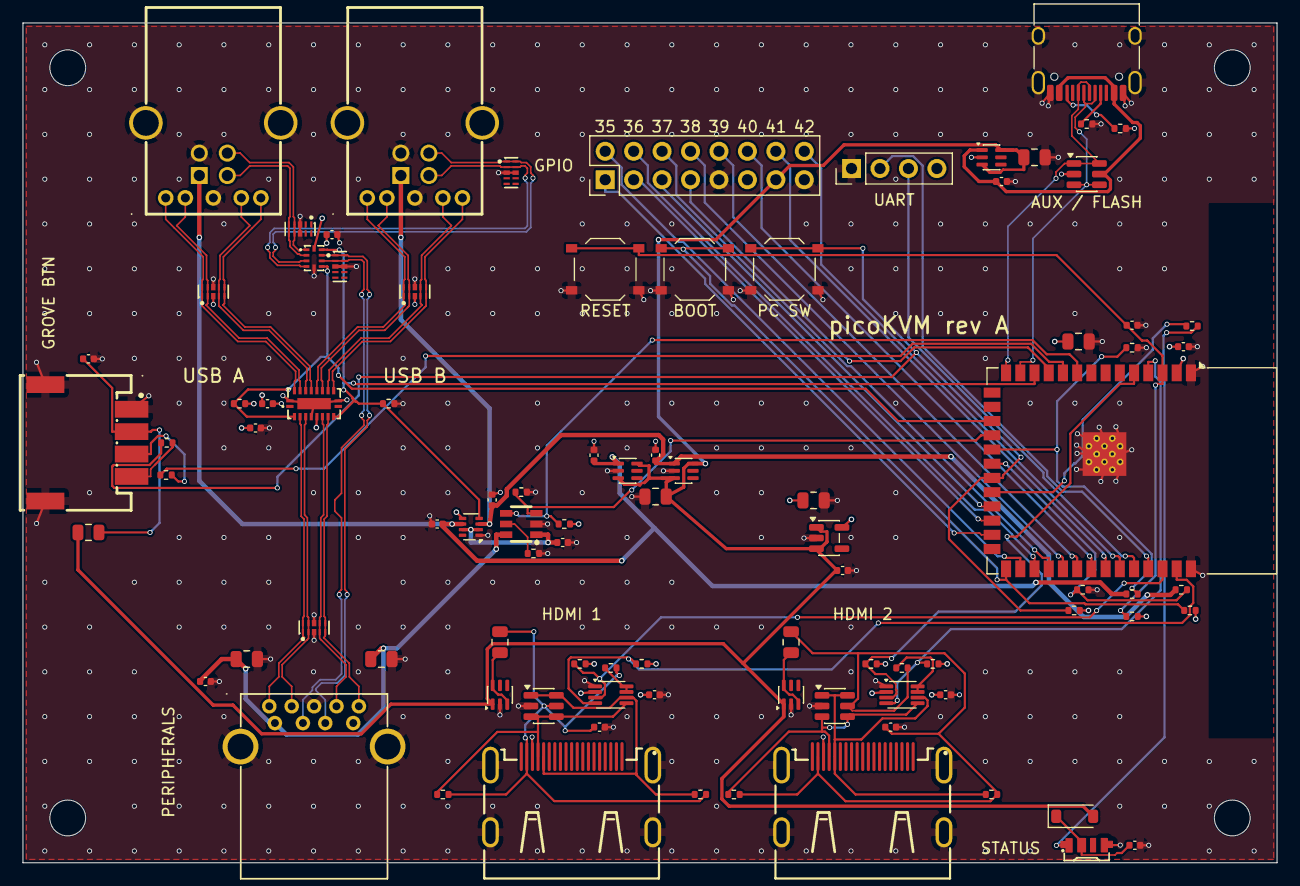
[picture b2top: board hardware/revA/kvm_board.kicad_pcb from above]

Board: 4 copper layers, 112.0 x 75.0 mm, 95 parts (0 on the bottom side), 75 nets.

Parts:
C1, C3, C6, C9, C14, C15, C16, C17, C19, C21, C22: 100nF; C_0402_1005Metric
C2, C4, C5, C10, C12, C20, C23, C24: 1uF; C_0402_1005Metric
C7, C8, C18: 22uF; C_0805_2012Metric
C11, C13, C25: 10uF; C_0805_2012Metric
D3: SK6812SIDE-A; LED-SMD_4P-L4.0-W1.6-L
D4: 1N4148W; D_SOD-123
F2, F3, F4: 100mA; Fuse_0805_2012Metric
H1, H2, H3, H4: MountingHole; MountingHole_3.2mm_M3
J1, J2: HC-USB3.0-L1845-BF; USB-B-TH_9P-L18.5-W12.0
J3: HC-USB3.0-L168-WP; USB-TH_USB3.0-A
J4: USB_C_Receptacle_USB2.0_16P; USB_C_Receptacle_HRO_TYPE-C-31-M-12
J5, J6: HDMI-001; HDMI-SMD_19P-P0.50-H-F
J7: UART; PinHeader_1x04_P2.54mm_Vertical
J8: GROVE_BTN; CONN-SMD_4P-P2.00_ZX-HY2.0-4PWT
J9: GPIO; PinHeader_2x08_P2.54mm_Vertical
R1, R2: 5.1k; R_0402_1005Metric
R3, R4, R6, R7, R8, R10, R22, R23, R24: 10k; R_0402_1005Metric
R5: 20k; R_0402_1005Metric
R9, R11: 15k; R_0402_1005Metric
R12, R17: 200k; R_0402_1005Metric
R13, R14, R18, R19: 4.7k; R_0402_1005Metric
R15, R16, R20, R21: 2k; R_0402_1005Metric
R25, R26, R27: 100; R_0402_1005Metric
SW1: RESET; SW_Push_1P1T_XKB_TS-1187A
SW2: BOOT; SW_Push_1P1T_XKB_TS-1187A
SW3: SWITCH; SW_Push_1P1T_XKB_TS-1187A
U1: ESP32-S3-WROOM-1-N8R2; ESP32-S3-WROOM-1
U2: HD3SS3212IRKSR; DHVQFN-20_L4.5-W2.5-P0.50-BL-EP
U3: TS3USB221ARSER; UQFN-10_L2.0-W1.5-P0.50-BL
U4: TPS2116DRL; SOT-583-8
U5: AP2112K-3.3; SOT-23-5
U6, U7, U8, U21, U22: LM66100DCK; SOT-363_SC-70-6
U9, U10: PCA9306DC; VSSOP-8_2.3x2mm_P0.5mm
U11, U12, U13, U17, U18, U19: TPD4E05U06DQAR_C138714; USON-10_L2.5-W1.0-P0.50-BL
U14, U15, U16: USBLC6-2SC6; SOT-23-6
U20: TPS2553DBVR; SOT-23-6_L2.9-W1.6-P0.95-LS2.8-BR

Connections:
+3V3: C1.1, C2.1, C3.1, C13.1, C15.1, C17.1, C18.1, C19.1, J7.4, J9.11, R4.2, R7.2, R13.2, R14.2, R18.2, R19.2, R22.2, R23.2, R24.2, U1.2, U2.6, U3.10, U4.5, U5.5, U9.2, U10.2
+5V_SYS: C11.1, C12.1, C25.1, D4.2, F4.1, J9.13, U5.1, U5.3, U6.3, U6.6, U7.3, U7.6, U8.3, U8.6, U21.1, U22.1
AUX_CC1: J4.A5, R1.1
AUX_CC2: J4.B5, R2.1
AUX_DN: J4.A7, J4.B7, U1.13, U14.3, U14.4
AUX_DP: J4.A6, J4.B6, U1.14, U14.1, U14.6
BOOT: R23.1, SW2.1, U1.27
BTN_SWITCH: R24.1, R26.1, SW3.1, U1.21
DDC1_SCL: R13.1, U1.38, U9.3
DDC1_SDA: R14.1, U1.39, U9.4
DDC1_VREF2: R12.1, U9.7, U9.8
DDC2_SCL: R18.1, U1.5, U10.3
DDC2_SDA: R19.1, U1.4, U10.4
DDC2_VREF2: R17.1, U10.7, U10.8
EN: C20.1, R22.1, SW1.1, U1.3
EXT_LED: R27.1, U1.10
GND: C1.2, C2.2, C3.2, C4.2, C5.2, C6.2, C7.2, C8.2, C9.2, C10.2, C11.2, C12.2, C13.2, C14.2, C15.2, C16.2, C17.2, C18.2, C19.2, C20.2, C21.2, C22.2, C23.2, C24.2, C25.2, D3.4, J1.4, J1.7, J1.10, J1.11, J2.4, J2.7, J2.10, J2.11, J3.4, J3.7, J3.10, J4.A1, J4.A12, J4.B1, J4.B12, J4.SH, J5.17, J5.20, J5.21, J5.22, J5.23, J6.17, J6.20, J6.21, J6.22, J6.23, J7.1, J8.1, J8.5, J8.6, J9.9, J9.15, R1.2, R2.2, R3.2, R5.2, R6.2, R9.2, R11.2, SW1.2, SW2.2, SW3.2, U1.1, U1.40, U1.41, U2.5, U2.11, U2.20, U2.21, U3.5, U4.1, U5.2, U6.2, U7.2, U8.2, U9.1, U10.1, U11.3, U11.8, U12.3, U12.8, U13.3, U13.8, U14.2, U15.2, U16.2, U17.3, U17.8, U18.3, U18.8, U19.3, U19.8, U20.2, U21.2, U22.2
GPIO18: J9.7, U1.11
GPIO21: J9.5, U1.23
GPIO35: J9.2, U1.28
GPIO36: J9.4, U1.29
GPIO37: J9.6, U1.30
GPIO38: J9.8, U1.31
GPIO39: J9.10, U1.32
GPIO40: J9.12, U1.33
GPIO41: J9.14, U1.34
GPIO42: J9.16, U1.35
GPIO47: J9.3, U1.24
GPIO48: J9.1, U1.25
GROVE_5V: C22.1, F4.2, J8.2
GROVE_BTN: J8.4, R26.2
GROVE_LED: J8.3, R27.2
HDMI1_5V: C14.1, F2.2, J5.18, R12.2, R15.2, R16.2, U15.5
HDMI1_5V_D: F2.1, U21.3, U21.6
HDMI1_SCL: J5.15, R15.1, U9.6, U15.1, U15.6
HDMI1_SDA: J5.16, R16.1, U9.5, U15.3, U15.4
HDMI2_5V: C16.1, F3.2, J6.18, R17.2, R20.2, R21.2, U16.5
HDMI2_5V_D: F3.1, U22.3, U22.6
HDMI2_SCL: J6.15, R20.1, U10.6, U16.1, U16.6
HDMI2_SDA: J6.16, R21.1, U10.5, U16.3, U16.4
LED_DIN: D3.1, R25.2
LED_RGB: R25.1, U1.22
LED_VDD: C21.1, D3.2, D4.1
PCA_DN: J1.2, U3.2, U11.5, U11.6
PCA_DP: J1.3, U3.1, U11.4, U11.7
PCA_SSRX_N: J1.8, U2.18, U17.2, U17.9
PCA_SSRX_P: J1.9, U2.19, U17.1, U17.10
PCA_SSTX_N: J1.5, U2.16, U17.5, U17.6
PCA_SSTX_P: J1.6, U2.17, U17.4, U17.7
PCB_DN: J2.2, U3.4, U12.2, U12.9
PCB_DP: J2.3, U3.3, U12.1, U12.10
PCB_SSRX_N: J2.8, U2.14, U18.2, U18.9
PCB_SSRX_P: J2.9, U2.15, U18.1, U18.10
PCB_SSTX_N: J2.5, U2.12, U18.5, U18.6
PCB_SSTX_P: J2.6, U2.13, U18.4, U18.7
PERIPH_EN: R6.1, U1.18, U20.3
PERIPH_FAULT_N: R7.1, U1.9, U20.4
PERIPH_ILIM: R5.1, U20.5
PER_DN: J3.2, U3.7, U13.2, U13.9
PER_DP: J3.3, U3.8, U13.1, U13.10
PER_SSRX_N: J3.5, U2.8, U19.5, U19.6
PER_SSRX_P: J3.6, U2.7, U19.4, U19.7
PER_SSTX_N: J3.8, U2.4, U19.2, U19.9
PER_SSTX_P: J3.9, U2.3, U19.1, U19.10
RXD0: J7.3, U1.36
TXD0: J7.2, U1.37
USB_OE_N: R4.1, U1.17, U2.2, U3.6
USB_SEL: R3.1, U1.12, U2.9, U3.9, U4.4
VBUS_A: C4.1, C23.1, J1.1, R8.1, U4.6, U6.1
VBUS_AUX: C10.1, J4.A4, J4.A9, J4.B4, J4.B9, U8.1, U14.5
VBUS_A_SENSE: R8.2, R9.1, U1.19
VBUS_B: C5.1, C24.1, J2.1, R10.1, U4.3, U7.1
VBUS_B_SENSE: R10.2, R11.1, U1.20
VBUS_PERIPH: C7.1, C8.1, C9.1, J3.1, U20.6
VBUS_PERIPH_RAW: C6.1, U4.2, U4.7, U20.1

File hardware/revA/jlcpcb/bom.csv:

Comment,Designator,Footprint,LCSC Part #
100nF,"C1,C3,C6,C9,C14,C15,C16,C17,C19,C21,C22",C_0402_1005Metric,C1525
1uF,"C2,C4,C5,C10,C12,C20,C23,C24",C_0402_1005Metric,C52923
22uF,"C7,C8,C18",C_0805_2012Metric,C45783
10uF,"C11,C13,C25",C_0805_2012Metric,C15850
SK6812SIDE-A,D3,LED-SMD_4P-L4.0-W1.6-L,C5378721
1N4148W,D4,D_SOD-123,C81598
100mA,"F2,F3,F4",Fuse_0805_2012Metric,C20975
HC-USB3.0-L1845-BF,"J1,J2",USB-B-TH_9P-L18.5-W12.0,C7501849
HC-USB3.0-L168-WP,J3,USB-TH_USB3.0-A,C7501850
USB_C_Receptacle_USB2.0_16P,J4,USB_C_Receptacle_HRO_TYPE-C-31-M-12,C165948
HDMI-001,"J5,J6",HDMI-SMD_19P-P0.50-H-F,C138388
UART,J7,PinHeader_1x04_P2.54mm_Vertical,C32713270
GROVE_BTN,J8,CONN-SMD_4P-P2.00_ZX-HY2.0-4PWT,C7429571
GPIO,J9,PinHeader_2x08_P2.54mm_Vertical,C68234
5.1k,"R1,R2",R_0402_1005Metric,C25905
10k,"R3,R4,R6,R7,R8,R10,R22,R23,R24",R_0402_1005Metric,C25744
20k,R5,R_0402_1005Metric,C25765
15k,"R9,R11",R_0402_1005Metric,C25756
200k,"R12,R17",R_0402_1005Metric,C25764
4.7k,"R13,R14,R18,R19",R_0402_1005Metric,C25900
2k,"R15,R16,R20,R21",R_0402_1005Metric,C4109
100,"R25,R26,R27",R_0402_1005Metric,C25076
BOOT/RESET/SWITCH,"SW1,SW2,SW3",SW_Push_1P1T_XKB_TS-1187A,C571338
ESP32-S3-WROOM-1-N8R2,U1,ESP32-S3-WROOM-1,C2913204
HD3SS3212IRKSR,U2,DHVQFN-20_L4.5-W2.5-P0.50-BL-EP,C544517
TS3USB221ARSER,U3,UQFN-10_L2.0-W1.5-P0.50-BL,C128396
TPS2116DRL,U4,SOT-583-8,C3235557
AP2112K-3.3,U5,SOT-23-5,C51118
LM66100DCK,"U6,U7,U8,U21,U22",SOT-363_SC-70-6,C2869734
PCA9306DC,"U9,U10",VSSOP-8_2.3x2mm_P0.5mm,C33196
TPD4E05U06DQAR_C138714,"U11,U12,U13,U17,U18,U19",USON-10_L2.5-W1.0-P0.50-BL,C138714
USBLC6-2SC6,"U14,U15,U16",SOT-23-6,C7519
TPS2553DBVR,U20,SOT-23-6_L2.9-W1.6-P0.95-LS2.8-BR,C55266

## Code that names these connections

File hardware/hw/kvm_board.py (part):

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pm["PR1"] += usb_sel
pm["MODE"] += v3
for pin in pm.get_pins("VOUT"):
    pin += vbus_pc
pm["GND"] += gnd
pm["ST"] += NC
C_ref("1uF", "C4", vbus_a, gnd, at=("U4", "VIN2"))
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pa["PR1"] += aux_pr1
pa["MODE"] += vbus_aux
for pin in pa.get_pins("VOUT"):
    pin += vbus_hub
pa["GND"] += gnd
pa["ST"] += NC
R("33k", vbus_aux, aux_pr1)
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# build may map them; output mode "0 = high impedance, 1 = low"), on the side
# of the chip that faces the ESP32, 220R in series against contention, idle
# high through 10k:
#   GPIO22  toggle: straight onto the PC-switch button line (BTN_SWITCH), so
#           it works with firmware that knows nothing about the RP2350
#   GPIO20  RP_LINK_TX   GPIO21  RP_LINK_RX   GPIO26  RP_LINK_ATTN
# With stock hid-remapper the three RP_LINK lines are plain hotkey outputs
# (e.g. "go to PC A" / "go to PC B" / spare).  For a richer protocol
# GPIO20 / GPIO21 are UART1 TX / RX (also I2C0 SDA / SCL) and GPIO26 is free
# as an attention / interrupt line; the ESP32 side can take any role.
btn = Net("BTN_SWITCH")
rp_link = {}
for gpio, net in ((22, btn), (20, Net("RP_LINK_TX")), (21, Net("RP_LINK_RX")),
                  (26, Net("RP_LINK_ATTN"))):
    at_rp = Net(f"RP_GPIO{gpio}")
    rp[f"GPIO{gpio}/ADC0" if gpio == 26 else f"GPIO{gpio}"] += at_rp
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
# activity LED (hid-remapper blinks GPIO25)
rp_led, rp_led_k = Net("RP_LED"), Net("RP_LED_K")
rp["GPIO25"] += rp_led
d5 = part("Device", "LED", footprint="LED_SMD:LED_0603_1608Metric", lcsc="C2286",
          value="KBD", ref="D5")
d5["A"] += rp_led
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rp["GPIO1"] += rp_hdn
R("27", rp_hdp, kbh["DP"])
R("27", rp_hdn, kbh["DN"])
R("8.2k", kbh["DP"], gnd, at=("U47", "4"))     # at U47's port-2 pins (2D-/2D+ carry KBH_DP/DN)
R("8.2k", kbh["DN"], gnd, at=("U47", "3"))
# device side: 27R in series (RP2350 datasheet)
rp_ddp, rp_ddn = Net("RP_USB_DP"), Net("RP_USB_DN")
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R("10k", btn, v3)

# Pins shared with rev A keep their GPIO where the function still exists;
# BOARD_REV tells the boards apart (rev A leaves GPIO15 open).  Differences
# from rev A (README.md, "Rev B: differences from rev A"): GPIO1 / GPIO2 are
# the I2C bus to the multiplexer U13 instead of HDMI 1's DDC, GPIO4 is the
# multiplexer's reset instead of HDMI 2's SDA, GPIO5 is free.
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
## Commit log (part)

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2025-02-07 Tentative devContainer
2025-02-07 Update devcontainer.json
    With a full python
2025-02-07 Linting
2025-02-07 Increase line length
2025-02-07 Read first response from WS before sending anything
2025-02-08 Fix power_on
2025-02-08 Fix linting
2025-02-08 Run set_input in parallel
2025-02-08 Sample config file
2025-02-08 Readme & fix command_delay
2025-02-08 Fix channel_uri
2025-02-08 Fix token aquisition flow
2025-02-08 Some mermaid
2025-02-08 Improve readme
2025-02-08 Update README.md
    Fix typo
2025-02-08 Typo
2025-02-08 Simplify JS
2025-02-09 Add blinking led, rename set_active_input
2025-02-09 Implement locking
2025-02-09 Fix order
2025-02-11 Move handle_client to webserver
2025-02-24 Add physical button mgmt
2025-02-24 Fix racing condition that led to the LED remaining on
2025-02-25 Properly cancel the blinking if case of exception
2025-02-28 Fix initial irq trigger on boot
2025-02-28 Introduce per-command delay
2025-02-28 Let readme reflect new config
2025-02-28 Fix typo
2025-02-28 Fix typos
2025-04-21 Switch from interupt to polling not to mess with asyncio
2025-04-21 Stop catching unnecessary exceptions
2025-04-21 Remove space
2025-04-22 Remove powerstate check as using KEY_POWER is not mandary for wake up Update readme & config accordingly
2025-04-22 Add timeout
2025-06-01 - Disable wifi power mgmt. - Rename set_active_input and get_active_input to active_input to be more REST
2025-06-01 Reuse aiohttp over different call.
2025-06-01 Revert "Reuse aiohttp over different call."
    This reverts commit b5aa8036a9db4efd8c93f0e05cf689e5125a7603.
2025-06-04 Add repeat in command dict
2025-06-04 Garbage collect
2025-06-06 Improve wifi reconnection
2025-06-06 Use constant for powersave, harmonize private attribute naming
2025-06-08 Add some debug
2025-06-14 Migration to Atom + minor improvements
2025-06-14 Fix sample config nesting
2025-06-15 Add some explicit garbage collecting to fight error 12
2025-06-20 Remove mdns lib as builtin feature is working
2025-06-20 Cleanup
2025-07-10 Static sslContext to save up on memory
2025-07-11 Fix naming
2025-07-12 Add metrics
2025-07-14 Change gc invocation strategy
2025-07-14 Add mcu temperature
2026-01-19 Fix API URL formatting in README.md
